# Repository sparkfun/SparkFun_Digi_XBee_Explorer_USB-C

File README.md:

SparkFun Digi XBee® Explorer USB-C
========================================

[*SparkFun Digi XBee® Explorer USB-C (22043)*](https://www.sparkfun.com/products/22043)

<Basic description of the part.>

Repository Contents
-------------------

* **/Hardware** - Eagle design files (.brd, .sch)
* **/Production** - Production panel files (.brd)

Documentation
--------------
* **[Hookup Guide](http://docs.sparkfun.com/SparkFun_Digi_XBee_Explorer_USB-C)** - Basic hookup guide for the SparkFun Digi XBee® Explorer USB-C.

License Information
-------------------

This product is _**open source**_! 

Please review the LICENSE.md file for license information. 

If you have any questions or concerns on licensing, please contact technical support on our [SparkFun forums](https://forum.sparkfun.com/viewforum.php?f=152).

Distributed as-is; no warranty is given.

- Your friends at SparkFun.

_<COLLABORATION CREDIT>_

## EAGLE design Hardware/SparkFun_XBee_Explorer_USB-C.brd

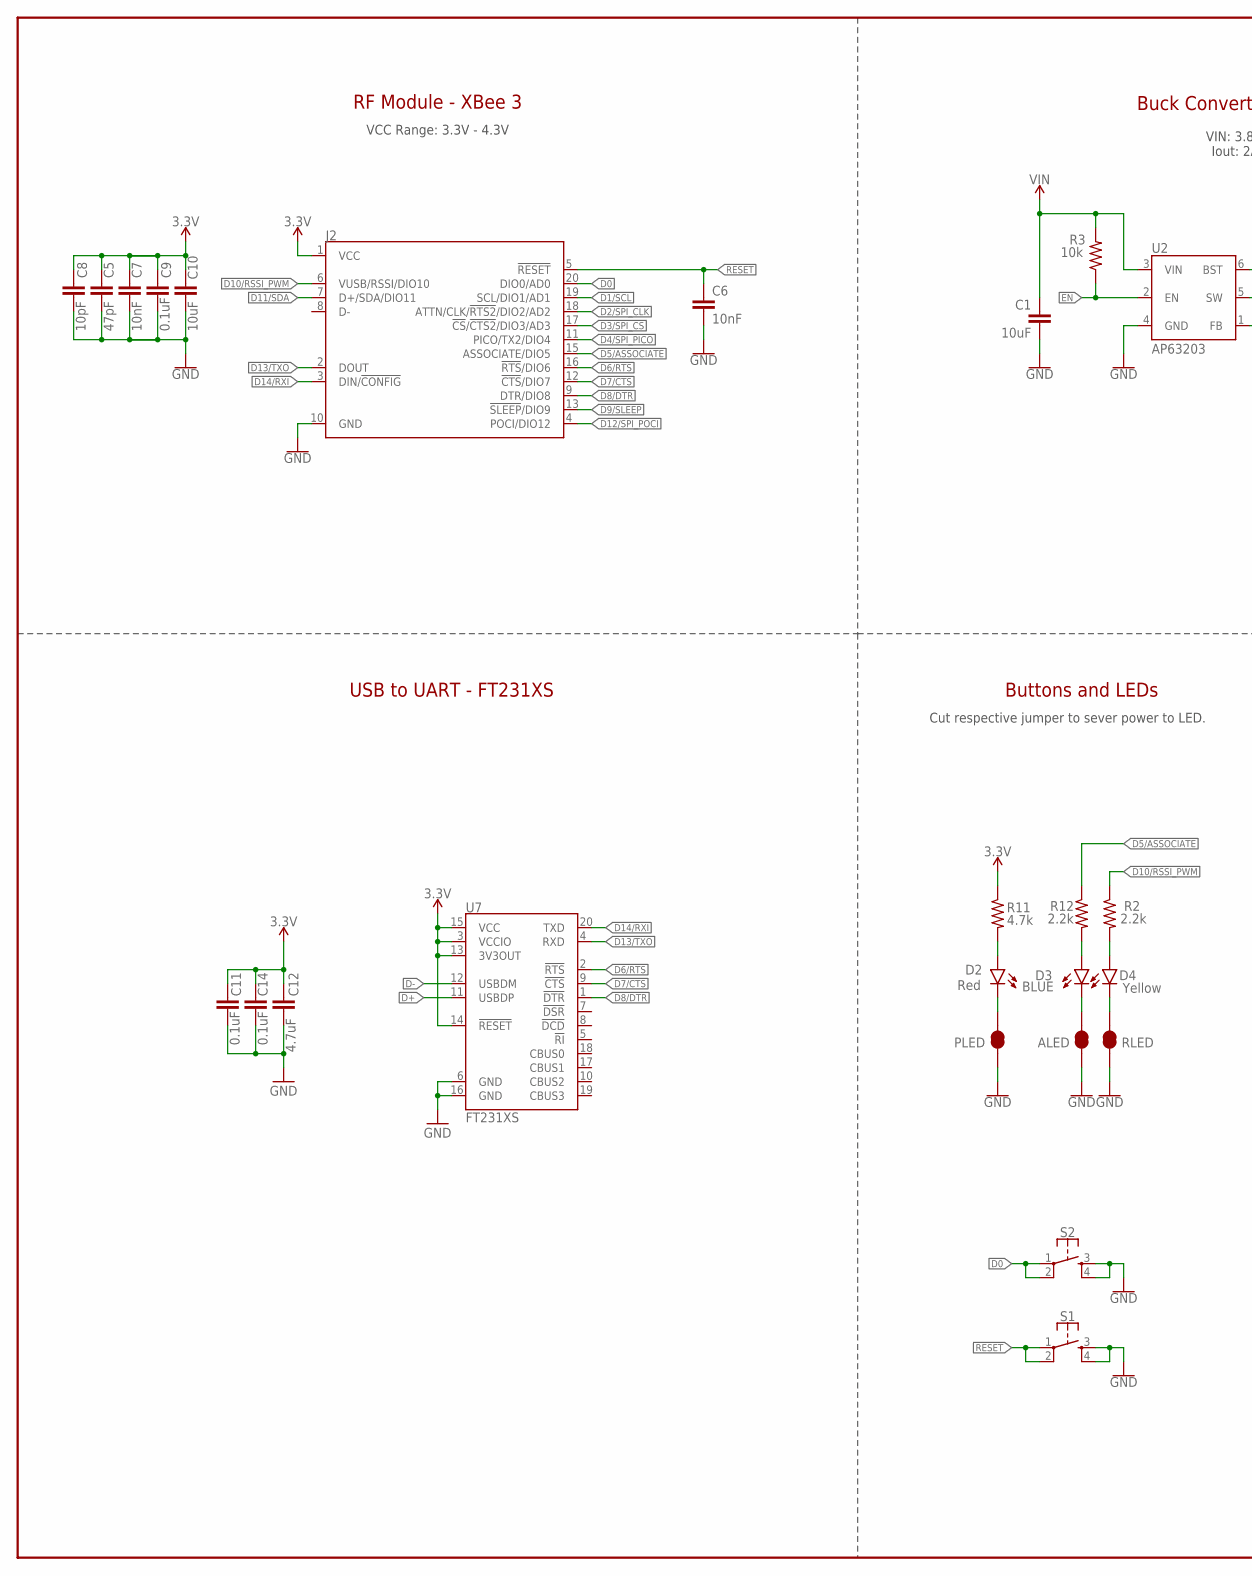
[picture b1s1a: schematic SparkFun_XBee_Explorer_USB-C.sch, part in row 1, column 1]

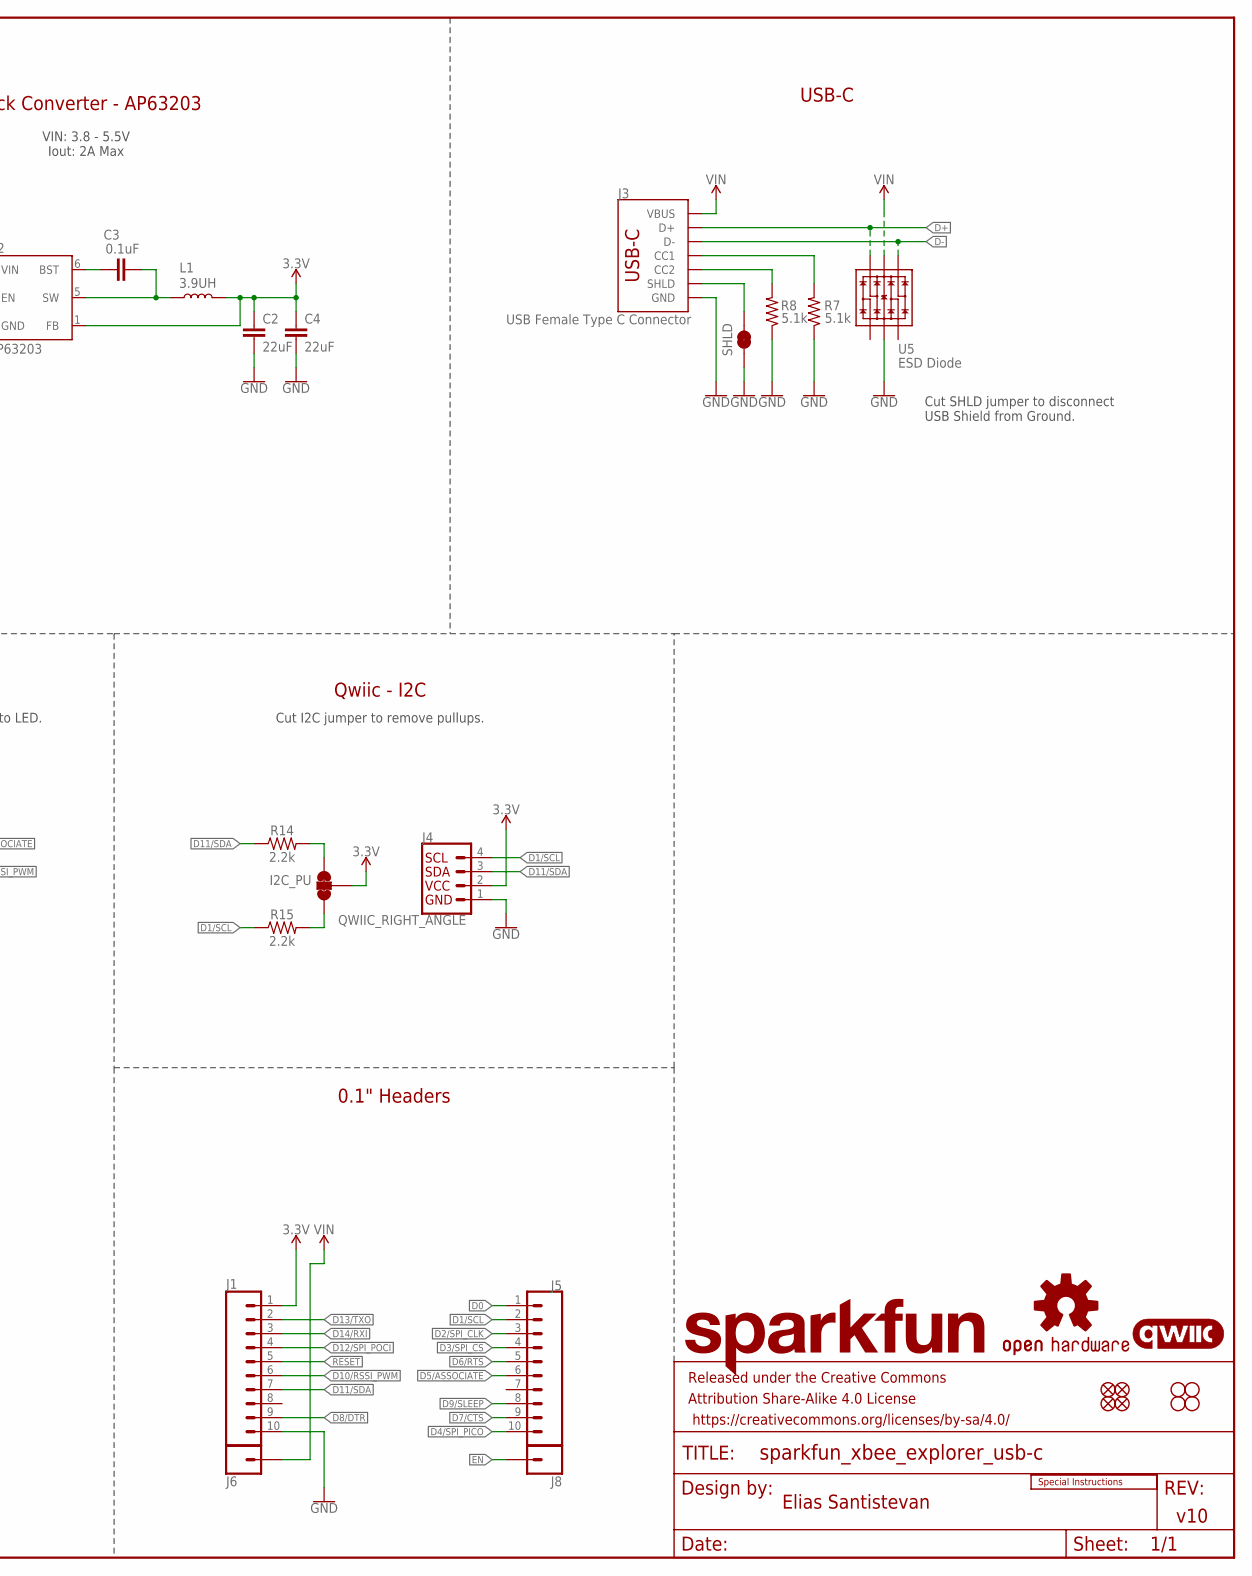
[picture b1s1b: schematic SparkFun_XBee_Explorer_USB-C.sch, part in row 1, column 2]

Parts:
ALED: JUMPER-SMT_2_NC_TRACE_SILK; SMT-JUMPER_2_NC_TRACE_SILK
C1: 10uF; 1210
C2, C4: 22uF; 0603
C3, C9, C11, C14: 0.1uF; 0603
C5: 47pF; 0603
C6, C7: 10nF; 0603
C8: 10pF; 0603
C10: 10uF; 0603
C12: 4.7uF; 0603
D2: Red; LED-0603
D3: BLUE; LED-0603
D4: Yellow; LED-0603
FD1, FD2, FD3, FD4: FIDUCIAL1X2; FIDUCIAL-1X2
FRAME1: FRAME-LEDGER; CREATIVE_COMMONS
H1, H2, H3, H4: STAND-OFFTIGHT; STAND-OFF-TIGHT
I2C_PU: JUMPER-SMT_3_2-NC_TRACE_SILK; SMT-JUMPER_3_2-NC_TRACE_SILK
J1, J8: CONN_01PTH_NO_SILK_STAND; 1X01_NO_SILK_STAND
J2: XBEE_UPDATEXBEE_SMD; XBEE3-SMD
J3: USB Female Type C Connector; USB-C-16P-4LAYER-ISOLATED
J4: QWIIC_RIGHT_ANGLE; JST04_1MM_RA
J5, J6: CONN_10NO_SILK_PTH_FEMALE; 1X10_NO_SILK
L1: 3.9UH; INDUCTOR_3.9UH
LOGO1: SFE_LOGO_NAME.2_INCH; SFE_LOGO_NAME_.2
LOGO2: OSHW-LOGOS; OSHW-LOGO-S
LOGO3: QWIIC_LOGO_4MM; QWIIC_4MM
LOGO4: SPECIAL_INSTRUCTIONS-ORDERING; ORDERING_INSTRUCTIONS
PLED: JUMPER-SMT_2_NC_TRACE_SILK; SMT-JUMPER_2_NC_TRACE_SILK
R2, R12, R14, R15: 2.2k; 0603
R3: 10k; 0603
R7, R8: 5.1k; 0603
R11: 4.7k; 0603
RLED: JUMPER-SMT_2_NC_TRACE_SILK; SMT-JUMPER_2_NC_TRACE_SILK
S1, S2: MOMENTARY-SWITCH-SPST-2-SMD-5.2MM-TALL; TACTILE_SWITCH_SMD_5.2MM
SHLD: JUMPER-SMT_2_NC_TRACE_SILK; SMT-JUMPER_2_NC_TRACE_SILK
U2: AP63203; SOT23-6
U5: ESD Diode; SOT-23-6
U7: FT231XS; SSOP20_L

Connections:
3.3V: C2.1, C4.1, C5.1, C7.1, C8.1, C9.1, C10.1, C11.1, C12.1, C14.1, I2C_PU.2, J2.1 (VCC), J4.2, J6.1, L1.P$2 (2), R11.1, U2.1 (FB), U7.3 (VCCIO), U7.13 (3V3OUT), U7.14 (!RESET), U7.15 (VCC)
!RESET!: C6.1, J2.5 (!RESET!), J6.5, S1.1, S1.2
D0: J2.20 (DIO0/AD0), J5.1, S2.1, S2.2
D1/SCL: J2.19 (SCL/DIO1/AD1), J4.4, J5.2, R15.1
D2/SPI_CLK: J2.18 (ATTN/CLK/!RTS2!/DIO2/AD2), J5.3
D3/SPI_!CS!: J2.17 (!CS!/!CTS2!/DIO3/AD3), J5.4
D4/SPI_PICO: J2.11 (PICO/TX2/DIO4), J5.10
D5/ASSOCIATE: J2.15 (ASSOCIATE/DIO5), J5.6, R12.1
D6/!RTS!: J2.16 (!RTS!/DIO6), J5.5, U7.2 (!RTS)
D7/!CTS!: J2.12 (!CTS!/DIO7), J5.9, U7.9 (!CTS)
D8/!DTR!: J2.9 (DTR/DIO8), J6.9, U7.1 (!DTR)
D9/!SLEEP!: J2.13 (!SLEEP!/DIO9), J5.8
D10/RSSI_PWM: J2.6 (VUSB/RSSI/DIO10), J6.6, R2.1
D11/SDA: J2.7 (D+/SDA/DIO11), J4.3, J6.7, R14.1
D12/SPI_POCI: J2.4 (POCI/DIO12), J6.4
D13/TXO: J2.2 (DOUT), J6.2, U7.4 (RXD)
D14/RXI: J2.3 (DIN/!CONFIG!), J6.3, U7.20 (TXD)
D+: J3.A6 (D+), J3.B6 (D+), U5.6 (IO4), U7.11 (USBDP)
D-: J3.A7 (D-), J3.B7 (D-), U5.4 (IO3), U7.12 (USBDM)
EN: J8.1, R3.1, U2.2 (EN)
GND: ALED.1, C1.2, C2.2, C4.2, C5.2, C6.2, C7.2, C8.2, C9.2, C10.2, C11.2, C12.2, C14.2, J2.10 (GND), J3.GND, J3.GND2 (GND), J4.1, J6.10, PLED.1, R7.1, R8.1, RLED.1, S1.3, S1.4, S2.3, S2.4, SHLD.1, U2.4 (GND), U5.2 (VSS), U7.6 (GND), U7.16 (GND)
unnamed: C3.1, U2.6 (BST)
unnamed: D4.A, R2.2
unnamed: D4.C, RLED.2
unnamed: J3.B5 (CC2), R8.2
unnamed: J3.A5 (CC1), R7.2
unnamed: D2.A, R11.2
unnamed: C3.2, L1.P$1 (1), U2.5 (SW)
unnamed: I2C_PU.3, R14.2
unnamed: D3.A, R12.2
unnamed: I2C_PU.1, R15.2
unnamed: ALED.2, D3.C
unnamed: D2.C, PLED.2
SHLD: J3.SHLD1 (SHLD), J3.SHLD2 (SHLD), J3.SHLD3 (SHLD), J3.SHLD4 (SHLD), J3.SHLD5 (SHLD), J3.SHLD6 (SHLD), J3.SHLD7 (SHLD), J3.SHLD8 (SHLD), SHLD.2
VIN: C1.1, J1.1, J3.VBUS1 (VBUS), J3.VBUS2 (VBUS), R3.2, U2.3 (VIN), U5.5 (VCC)

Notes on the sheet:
VCC Range: 3.3V - 4.3V
Buck Converter - AP63203
Qwiic - I2C
v10
Elias Santistevan
Buttons and LEDs
VIN: 3.8 - 5.5V Iout: 2A Max
Cut I2C jumper to remove pullups.
Cut respective jumper to sever power to LED.
RF Module - XBee 3
0.1" Headers
Cut SHLD jumper to disconnect USB Shield from Ground.
USB to UART - FT231XS
USB-C

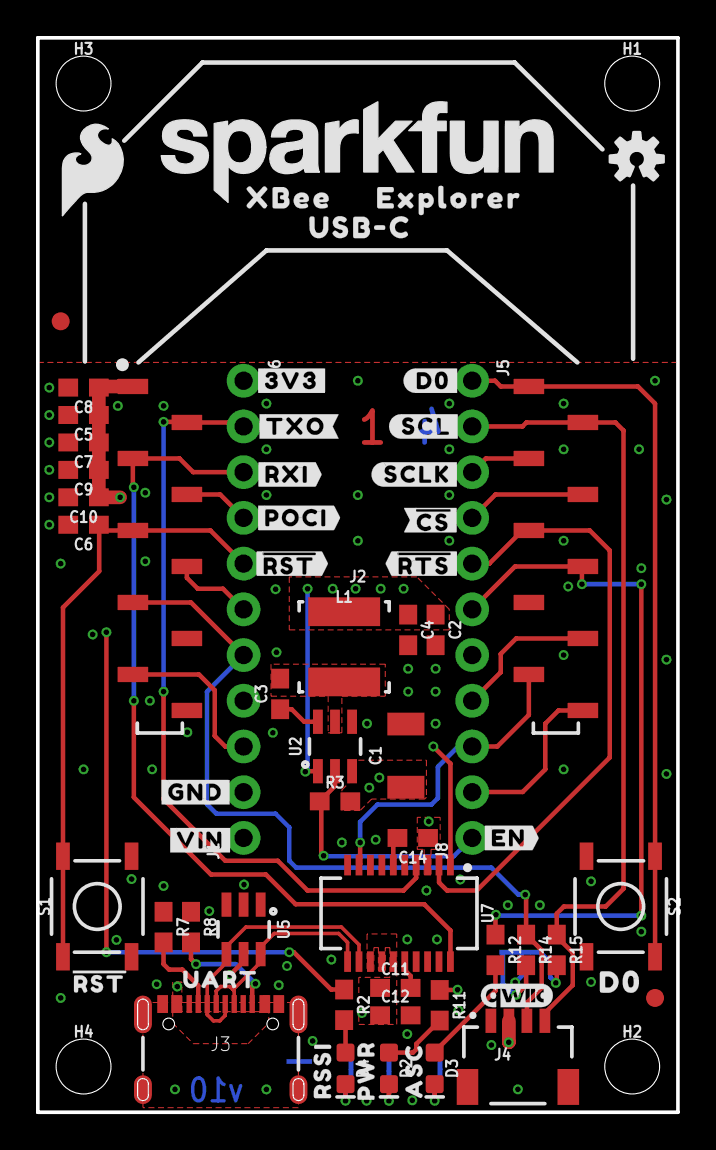
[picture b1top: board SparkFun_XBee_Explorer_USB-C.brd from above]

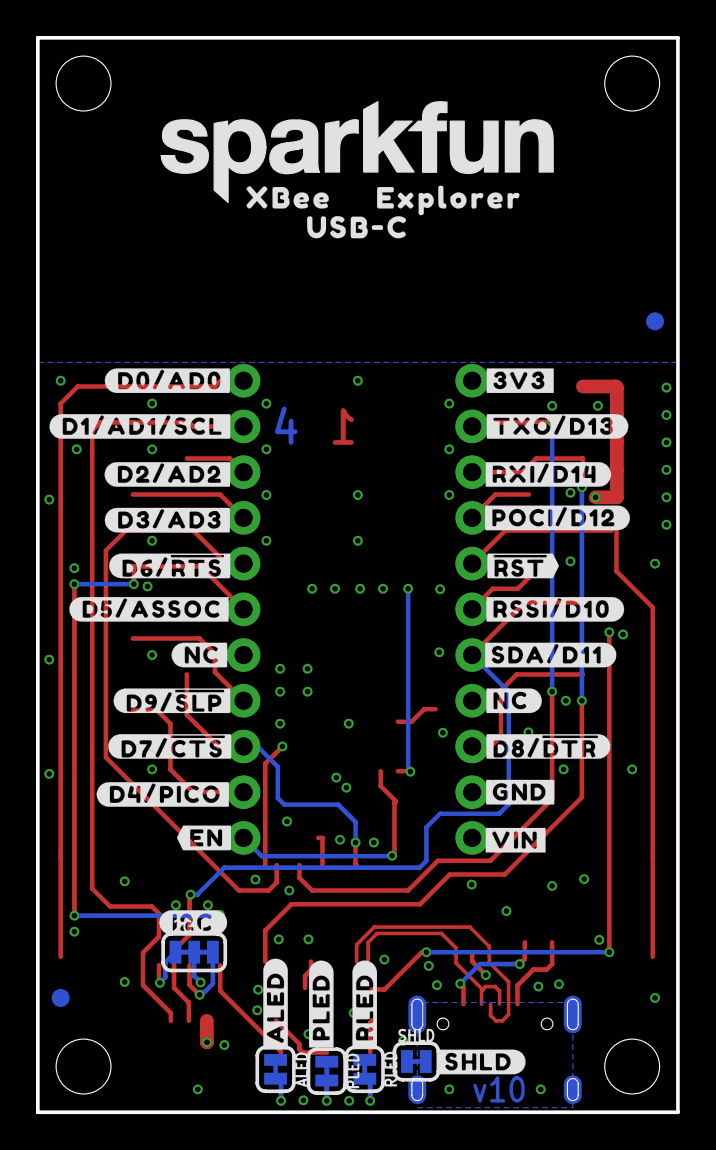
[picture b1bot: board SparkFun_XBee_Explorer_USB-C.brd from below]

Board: 4 copper layers, 35.6 x 59.7 mm, 109 parts (38 on the bottom side), 35 nets.

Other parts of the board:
U$1: RSSI31
U$2: PWR29
U$3, U$12: #GND#0
U$4: #SHLD#36
U$5: #NC#1
U$6: #D3#AD3#23
U$7: #NC#3
U$8: #D0#AD0#18
U$9, U$44: #3V3#1
U$10, U$23: XBEE340
U$11: #D1#AD1#SCL#8
U$13: #D8##DTR##27
U$14: #RSSI#D10#17
U$15: #SDA#D11#9
U$16: ##RST##15
U$17: #POCI#D12#24
U$18: #RXI#D14#15
U$19: #D2#AD2#19
U$20: #D6##RTS##25
U$21: #TXO#8
U$22: #TXO#D13#13
U$24, U$25: USB#C1342
U$26: #I2C#33
U$27: #RXI#7
U$28: UART34
U$29: ASC32
U$30: #RST#30
U$31, U$32: EXPLORER1344
U$35: #D5#ASSOC#25
U$36: #D9##SLP##28
U$37: #D7##CTS##26
U$38: #D4#PICO#25
U$40: D03
U$45: #POCI#32
U$46, U$66: #VIN#4
U$48: #EN#17
U$49: #ALED#21
U$51: #RLED#22
U$52: #PLED#20
U$54: ##RST##13
U$58: ##RTS##14
U$59: ##CS##26
U$60: #SCLK#33
U$61: SFE_LOGO_FLAME_.2
U$63: SFE_LOGO_NAME_.2
U$64: #SCL#9
U$65: #D0#3
U$67: #EN#15

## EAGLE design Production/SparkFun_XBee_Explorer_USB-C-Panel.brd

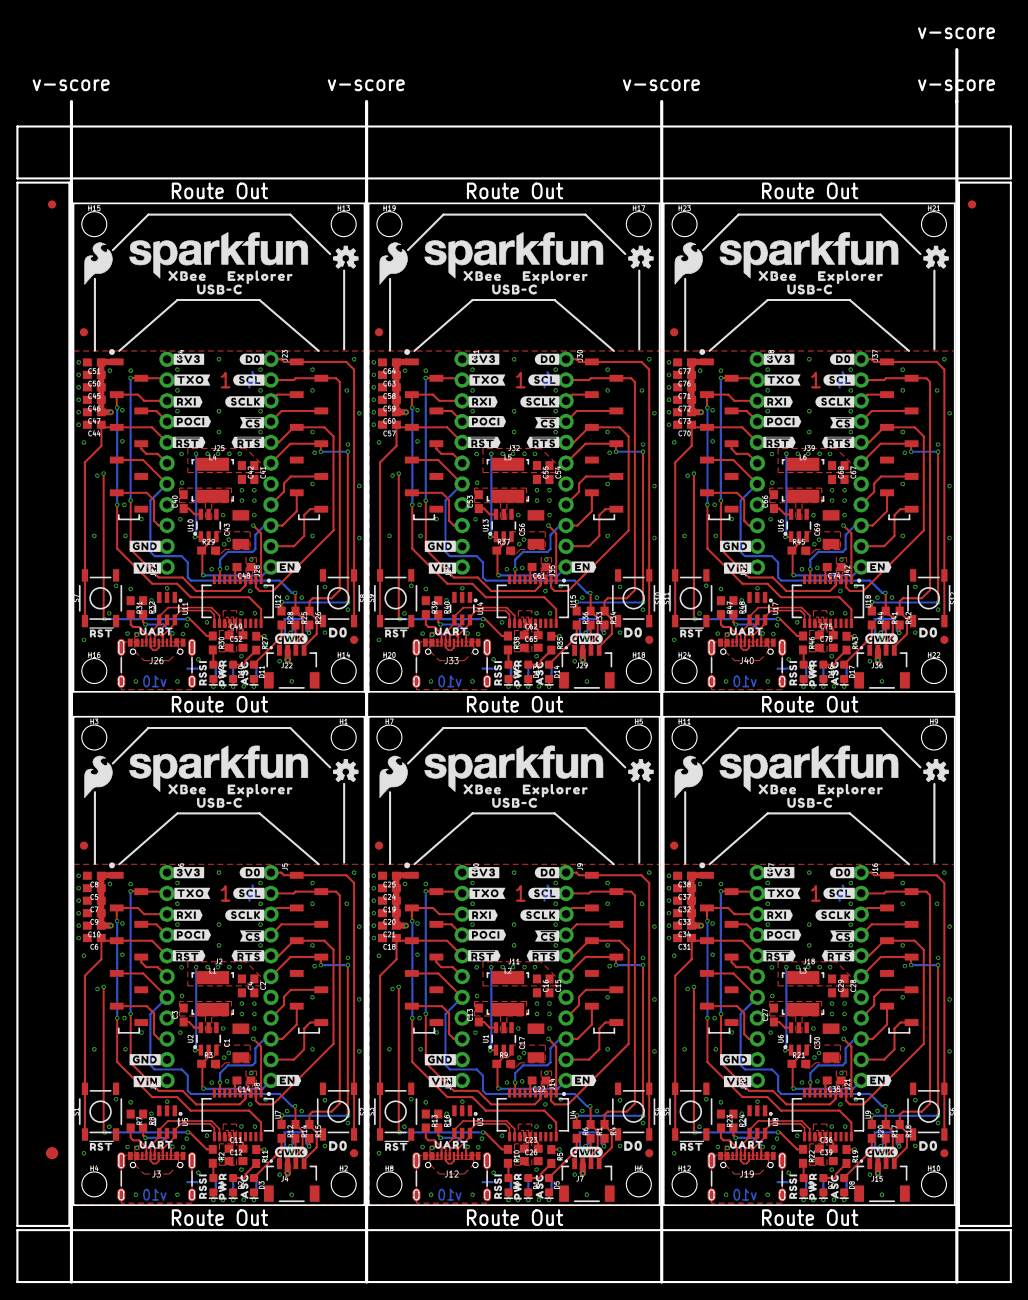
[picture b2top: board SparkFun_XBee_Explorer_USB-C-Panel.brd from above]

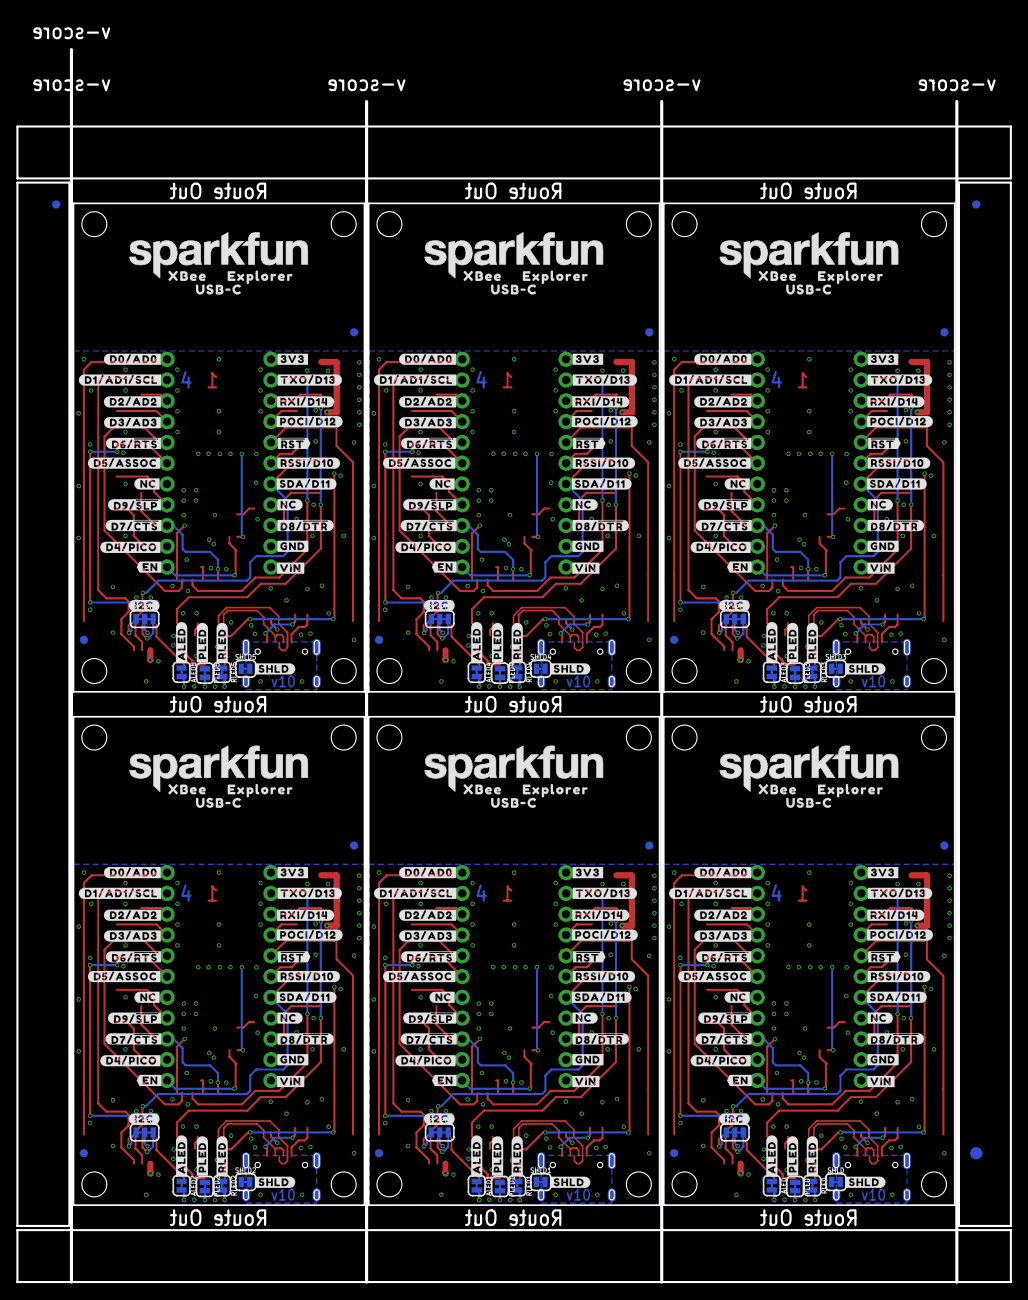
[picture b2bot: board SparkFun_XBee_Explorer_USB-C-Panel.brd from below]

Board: 4 copper layers, 121.4 x 150.6 mm, 648 parts (231 on the bottom side), 210 nets.

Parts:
ALED, ALED1, ALED2, ALED3, ALED4, ALED5: JUMPER-SMT_2_NC_TRACE_SILK; SMT-JUMPER_2_NC_TRACE_SILK
C1, C17, C30, C43, C56, C69: 10uF; 1210
C2, C4, C15, C16, C28, C29, C41, C42, C54, C55, C67, C68: 22uF; 0603
C3, C9, C11, C13, C14, C20, C22, C23, C27, C33, C35, C36, C40, C46, C48, C49, C53, C59, C61, C62, C66, C72, C74, C75: 0.1uF; 0603
C5, C24, C37, C50, C63, C76: 47pF; 0603
C6, C7, C18, C19, C31, C32, C44, C45, C57, C58, C70, C71: 10nF; 0603
C8, C25, C38, C51, C64, C77: 10pF; 0603
C10, C21, C34, C47, C60, C73: 10uF; 0603
C12, C26, C39, C52, C65, C78: 4.7uF; 0603
D1, D2, D7, D10, D13, D16: Red; LED-0603
D3, D5, D8, D11, D14, D17: BLUE; LED-0603
D4, D6, D9, D12, D15, D18: Yellow; LED-0603
E$1, E$2, E$3, E$4: FIDUCIAL-1X2
E$5, E$6: FIDUCIAL-1.5X3
FD1, FD2, FD3, FD4, FD5, FD6, FD7, FD8, FD9, FD10, FD11, FD12, FD13, FD14, FD15, FD16, FD17, FD18, FD19, FD20, FD21, FD22, FD23, FD24: FIDUCIAL1X2; FIDUCIAL-1X2
H1, H2, H3, H4, H5, H6, H7, H8, H9, H10, H11, H12, H13, H14, H15, H16, H17, H18, H19, H20, H21, H22, H23, H24: STAND-OFFTIGHT; STAND-OFF-TIGHT
I2C_PU, I2C_PU1, I2C_PU2, I2C_PU3, I2C_PU4, I2C_PU5: JUMPER-SMT_3_2-NC_TRACE_SILK; SMT-JUMPER_3_2-NC_TRACE_SILK
J1, J8, J13, J14, J20, J21, J27, J28, J34, J35, J41, J42: 1X01_NO_SILK_STAND
J2, J11, J18, J25, J32, J39: XBEE3-SMD
J3, J12, J19, J26, J33, J40: USB Female Type C Connector; USB-C-16P-4LAYER-ISOLATED
J4, J7, J15, J22, J29, J36: QWIIC_RIGHT_ANGLE; JST04_1MM_RA
J5, J6, J9, J10, J16, J17, J23, J24, J30, J31, J37, J38: 1X10_NO_SILK
L1, L2, L3, L4, L5, L6: 3.9UH; INDUCTOR_3.9UH
LOGO1, LOGO6, LOGO9, LOGO12, LOGO15, LOGO18: SFE_LOGO_NAME.2_INCH; SFE_LOGO_NAME_.2
LOGO2, LOGO4, LOGO7, LOGO10, LOGO13, LOGO16: OSHW-LOGOS; OSHW-LOGO-S
LOGO3, LOGO5, LOGO8, LOGO11, LOGO14, LOGO17: QWIIC_LOGO_4MM; QWIIC_4MM
PLED, PLED1, PLED2, PLED3, PLED4, PLED5: JUMPER-SMT_2_NC_TRACE_SILK; SMT-JUMPER_2_NC_TRACE_SILK
R1, R2, R4, R6, R10, R12, R14, R15, R17, R18, R20, R22, R25, R26, R28, R30, R33, R34, R36, R38, R41, R42, R44, R46: 2.2k; 0603
R3, R9, R21, R29, R37, R45: 10k; 0603
R5, R11, R19, R27, R35, R43: 4.7k; 0603
R7, R8, R13, R16, R23, R24, R31, R32, R39, R40, R47, R48: 5.1k; 0603
RLED, RLED1, RLED2, RLED3, RLED4, RLED5: JUMPER-SMT_2_NC_TRACE_SILK; SMT-JUMPER_2_NC_TRACE_SILK
S1, S2, S3, S4, S5, S6, S7, S8, S9, S10, S11, S12: TACTILE_SWITCH_SMD_5.2MM
SHLD, SHLD1, SHLD2, SHLD3, SHLD4, SHLD5: JUMPER-SMT_2_NC_TRACE_SILK; SMT-JUMPER_2_NC_TRACE_SILK
U1, U2, U6, U10, U13, U16: AP63203; SOT23-6
U3, U5, U8, U11, U14, U17: ESD Diode; SOT-23-6
U4, U7, U9, U12, U15, U18: FT231XS; SSOP20_L
U$1, U$104, U$158, U$212, U$266, U$320: RSSI31
U$2, U$105, U$159, U$213, U$267, U$321: PWR29
U$3, U$12, U$71, U$100, U$125, U$154, U$179, U$208, U$233, U$262, U$287, U$316: #GND#0
U$4, U$94, U$148, U$202, U$256, U$310: #SHLD#36
U$5, U$95, U$149, U$203, U$257, U$311: #NC#1
U$6, U$56, U$119, U$173, U$227, U$281: #D3#AD3#23
U$7, U$96, U$150, U$204, U$258, U$312: #NC#3
U$8, U$53, U$117, U$171, U$225, U$279: #D0#AD0#18
U$9, U$33, U$39, U$44, U$109, U$111, U$163, U$165, U$217, U$219, U$271, U$273: #3V3#1
U$10, U$23, U$101, U$102, U$155, U$156, U$209, U$210, U$263, U$264, U$317, U$318: XBEE340
U$11, U$106, U$160, U$214, U$268, U$322: #D1#AD1#SCL#8
U$13, U$72, U$126, U$180, U$234, U$288: #D8##DTR##27
U$14, U$73, U$127, U$181, U$235, U$289: #RSSI#D10#17
U$15, U$74, U$128, U$182, U$236, U$290: #SDA#D11#9
U$16, U$75, U$129, U$183, U$237, U$291: ##RST##15
U$17, U$76, U$130, U$184, U$238, U$292: #POCI#D12#24
U$18, U$77, U$131, U$185, U$239, U$293: #RXI#D14#15
U$19, U$55, U$118, U$172, U$226, U$280: #D2#AD2#19
U$20, U$57, U$120, U$174, U$228, U$282: #D6##RTS##25
U$21, U$83, U$137, U$191, U$245, U$299: #TXO#8
U$22, U$78, U$132, U$186, U$240, U$294: #TXO#D13#13
U$24, U$25, U$97, U$98, U$151, U$152, U$205, U$206, U$259, U$260, U$313, U$314: USB#C1342
U$26, U$34, U$110, U$164, U$218, U$272: #I2C#33
U$27, U$84, U$138, U$192, U$246, U$300: #RXI#7
U$28, U$99, U$153, U$207, U$261, U$315: UART34
U$29, U$103, U$157, U$211, U$265, U$319: ASC32
U$30, U$43, U$114, U$168, U$222, U$276: #RST#30
U$31, U$32, U$107, U$108, U$161, U$162, U$215, U$216, U$269, U$270, U$323, U$324: EXPLORER1344
U$35, U$62, U$121, U$175, U$229, U$283: #D5#ASSOC#25
U$36, U$68, U$122, U$176, U$230, U$284: #D9##SLP##28
U$37, U$69, U$123, U$177, U$231, U$285: #D7##CTS##26
U$38, U$70, U$124, U$178, U$232, U$286: #D4#PICO#25
U$40, U$42, U$113, U$167, U$221, U$275: D03
U$41, U$46, U$66, U$92, U$112, U$146, U$166, U$200, U$220, U$254, U$274, U$308: #VIN#4
U$45, U$85, U$139, U$193, U$247, U$301: #POCI#32
U$47, U$63, U$115, U$169, U$223, U$277: SFE_LOGO_NAME_.2
U$48, U$79, U$133, U$187, U$241, U$295: #EN#17
U$49, U$80, U$134, U$188, U$242, U$296: #ALED#21
U$50, U$61, U$116, U$170, U$224, U$278: SFE_LOGO_FLAME_.2
U$51, U$81, U$135, U$189, U$243, U$297: #RLED#22
U$52, U$82, U$136, U$190, U$244, U$298: #PLED#20
U$54, U$86, U$140, U$194, U$248, U$302: ##RST##13
U$58, U$87, U$141, U$195, U$249, U$303: ##RTS##14
U$59, U$88, U$142, U$196, U$250, U$304: ##CS##26
U$60, U$89, U$143, U$197, U$251, U$305: #SCLK#33
U$64, U$90, U$144, U$198, U$252, U$306: #SCL#9
U$65, U$91, U$145, U$199, U$253, U$307: #D0#3
U$67, U$93, U$147, U$201, U$255, U$309: #EN#15

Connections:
3.3V: C2.1, C4.1, C5.1, C7.1, C8.1, C9.1, C10.1, C11.1, C12.1, C14.1, I2C_PU.2, J2.1, J4.2, J6.1, L1.P$2, R11.1, U2.1, U7.3, U7.13, U7.14, U7.15
3.3V1: C15.1, C16.1, C19.1, C20.1, C21.1, C22.1, C23.1, C24.1, C25.1, C26.1, I2C_PU1.2, J7.2, J10.1, J11.1, L2.P$2, R5.1, U1.1, U4.3, U4.13, U4.14, U4.15
3.3V2: C28.1, C29.1, C32.1, C33.1, C34.1, C35.1, C36.1, C37.1, C38.1, C39.1, I2C_PU2.2, J15.2, J17.1, J18.1, L3.P$2, R19.1, U6.1, U9.3, U9.13, U9.14, U9.15
3.3V3: C41.1, C42.1, C45.1, C46.1, C47.1, C48.1, C49.1, C50.1, C51.1, C52.1, I2C_PU3.2, J22.2, J24.1, J25.1, L4.P$2, R27.1, U10.1, U12.3, U12.13, U12.14, U12.15
3.3V4: C54.1, C55.1, C58.1, C59.1, C60.1, C61.1, C62.1, C63.1, C64.1, C65.1, I2C_PU4.2, J29.2, J31.1, J32.1, L5.P$2, R35.1, U13.1, U15.3, U15.13, U15.14, U15.15
3.3V5: C67.1, C68.1, C71.1, C72.1, C73.1, C74.1, C75.1, C76.1, C77.1, C78.1, I2C_PU5.2, J36.2, J38.1, J39.1, L6.P$2, R43.1, U16.1, U18.3, U18.13, U18.14, U18.15
!RESET!: C6.1, J2.5, J6.5, S1.1, S1.2
!RESET!1: C18.1, J10.5, J11.5, S3.1, S3.2
!RESET!2: C31.1, J17.5, J18.5, S5.1, S5.2
!RESET!3: C44.1, J24.5, J25.5, S7.1, S7.2
!RESET!4: C57.1, J31.5, J32.5, S9.1, S9.2
!RESET!5: C70.1, J38.5, J39.5, S11.1, S11.2
D0: J2.20, J5.1, S2.1, S2.2
D1: J9.1, J11.20, S4.1, S4.2
D1/SCL: J2.19, J4.4, J5.2, R15.1
D1/SCL1: J7.4, J9.2, J11.19, R4.1
D1/SCL2: J15.4, J16.2, J18.19, R18.1
D1/SCL3: J22.4, J23.2, J25.19, R26.1
D1/SCL4: J29.4, J30.2, J32.19, R34.1
D1/SCL5: J36.4, J37.2, J39.19, R42.1
D2: J16.1, J18.20, S6.1, S6.2
D2/SPI_CLK: J2.18, J5.3
D2/SPI_CLK1: J9.3, J11.18
D2/SPI_CLK2: J16.3, J18.18
D2/SPI_CLK3: J23.3, J25.18
D2/SPI_CLK4: J30.3, J32.18
D2/SPI_CLK5: J37.3, J39.18
D3: J23.1, J25.20, S8.1, S8.2
D3/SPI_!CS!: J2.17, J5.4
D3/SPI_!CS!1: J9.4, J11.17
D3/SPI_!CS!2: J16.4, J18.17
D3/SPI_!CS!3: J23.4, J25.17
D3/SPI_!CS!4: J30.4, J32.17
D3/SPI_!CS!5: J37.4, J39.17
D4: J30.1, J32.20, S10.1, S10.2
D4/SPI_PICO: J2.11, J5.10
D4/SPI_PICO1: J9.10, J11.11
D4/SPI_PICO2: J16.10, J18.11
D4/SPI_PICO3: J23.10, J25.11
D4/SPI_PICO4: J30.10, J32.11
D4/SPI_PICO5: J37.10, J39.11
D5: J37.1, J39.20, S12.1, S12.2
D5/ASSOCIATE: J2.15, J5.6, R12.1
D5/ASSOCIATE1: J9.6, J11.15, R6.1
D5/ASSOCIATE2: J16.6, J18.15, R20.1
D5/ASSOCIATE3: J23.6, J25.15, R28.1
D5/ASSOCIATE4: J30.6, J32.15, R36.1
D5/ASSOCIATE5: J37.6, J39.15, R44.1
D6/!RTS!: J2.16, J5.5, U7.2
D6/!RTS!1: J9.5, J11.16, U4.2
D6/!RTS!2: J16.5, J18.16, U9.2
D6/!RTS!3: J23.5, J25.16, U12.2
D6/!RTS!4: J30.5, J32.16, U15.2
D6/!RTS!5: J37.5, J39.16, U18.2
D7/!CTS!: J2.12, J5.9, U7.9
D7/!CTS!1: J9.9, J11.12, U4.9
D7/!CTS!2: J16.9, J18.12, U9.9
D7/!CTS!3: J23.9, J25.12, U12.9
D7/!CTS!4: J30.9, J32.12, U15.9
D7/!CTS!5: J37.9, J39.12, U18.9
D8/!DTR!: J2.9, J6.9, U7.1
D8/!DTR!1: J10.9, J11.9, U4.1
D8/!DTR!2: J17.9, J18.9, U9.1
D8/!DTR!3: J24.9, J25.9, U12.1
D8/!DTR!4: J31.9, J32.9, U15.1
D8/!DTR!5: J38.9, J39.9, U18.1
D9/!SLEEP!: J2.13, J5.8
D9/!SLEEP!1: J9.8, J11.13
D9/!SLEEP!2: J16.8, J18.13
D9/!SLEEP!3: J23.8, J25.13
D9/!SLEEP!4: J30.8, J32.13
D9/!SLEEP!5: J37.8, J39.13
D10/RSSI_PWM: J2.6, J6.6, R2.1
D10/RSSI_PWM1: J10.6, J11.6, R10.1
D10/RSSI_PWM2: J17.6, J18.6, R22.1
D10/RSSI_PWM3: J24.6, J25.6, R30.1
D10/RSSI_PWM4: J31.6, J32.6, R38.1
D10/RSSI_PWM5: J38.6, J39.6, R46.1
D11/SDA: J2.7, J4.3, J6.7, R14.1
D11/SDA1: J7.3, J10.7, J11.7, R1.1
D11/SDA2: J15.3, J17.7, J18.7, R17.1
D11/SDA3: J22.3, J24.7, J25.7, R25.1
D11/SDA4: J29.3, J31.7, J32.7, R33.1
D11/SDA5: J36.3, J38.7, J39.7, R41.1
D12/SPI_POCI: J2.4, J6.4
D12/SPI_POCI1: J10.4, J11.4
D12/SPI_POCI2: J17.4, J18.4
D12/SPI_POCI3: J24.4, J25.4
D12/SPI_POCI4: J31.4, J32.4
D12/SPI_POCI5: J38.4, J39.4
D13/TXO: J2.2, J6.2, U7.4
D13/TXO1: J10.2, J11.2, U4.4
D13/TXO2: J17.2, J18.2, U9.4
D13/TXO3: J24.2, J25.2, U12.4
D13/TXO4: J31.2, J32.2, U15.4
D13/TXO5: J38.2, J39.2, U18.4
D14/RXI: J2.3, J6.3, U7.20
D14/RXI1: J10.3, J11.3, U4.20
D14/RXI2: J17.3, J18.3, U9.20
D14/RXI3: J24.3, J25.3, U12.20
D14/RXI4: J31.3, J32.3, U15.20
D14/RXI5: J38.3, J39.3, U18.20
D+: J3.A6, J3.B6, U5.6, U7.11
D+1: J12.A6, J12.B6, U3.6, U4.11
D+2: J19.A6, J19.B6, U8.6, U9.11
D+3: J26.A6, J26.B6, U11.6, U12.11
D+4: J33.A6, J33.B6, U14.6, U15.11
D+5: J40.A6, J40.B6, U17.6, U18.11
D-: J3.A7, J3.B7, U5.4, U7.12
D-1: J12.A7, J12.B7, U3.4, U4.12
D-2: J19.A7, J19.B7, U8.4, U9.12
D-3: J26.A7, J26.B7, U11.4, U12.12
D-4: J33.A7, J33.B7, U14.4, U15.12
D-5: J40.A7, J40.B7, U17.4, U18.12
EN: J8.1, R3.1, U2.2
EN1: J14.1, R9.1, U1.2
EN2: J21.1, R21.1, U6.2
EN3: J28.1, R29.1, U10.2
EN4: J35.1, R37.1, U13.2
EN5: J42.1, R45.1, U16.2
GND: ALED.1, C1.2, C2.2, C4.2, C5.2, C6.2, C7.2, C8.2, C9.2, C10.2, C11.2, C12.2, C14.2, J2.10, J3.GND, J3.GND2, J4.1, J6.10, PLED.1, R7.1, R8.1, RLED.1, S1.3, S1.4, S2.3, S2.4, SHLD.1, U2.4, U5.2, U7.6, U7.16
GND1: ALED1.1, C15.2, C16.2, C17.2, C18.2, C19.2, C20.2, C21.2, C22.2, C23.2, C24.2, C25.2, C26.2, J7.1, J10.10, J11.10, J12.GND, J12.GND2, PLED1.1, R13.1, R16.1, RLED1.1, S3.3, S3.4, S4.3, S4.4, SHLD1.1, U1.4, U3.2, U4.6, U4.16
GND2: ALED2.1, C28.2, C29.2, C30.2, C31.2, C32.2, C33.2, C34.2, C35.2, C36.2, C37.2, C38.2, C39.2, J15.1, J17.10, J18.10, J19.GND, J19.GND2, PLED2.1, R23.1, R24.1, RLED2.1, S5.3, S5.4, S6.3, S6.4, SHLD2.1, U6.4, U8.2, U9.6, U9.16
GND3: ALED3.1, C41.2, C42.2, C43.2, C44.2, C45.2, C46.2, C47.2, C48.2, C49.2, C50.2, C51.2, C52.2, J22.1, J24.10, J25.10, J26.GND, J26.GND2, PLED3.1, R31.1, R32.1, RLED3.1, S7.3, S7.4, S8.3, S8.4, SHLD3.1, U10.4, U11.2, U12.6, U12.16
GND4: ALED4.1, C54.2, C55.2, C56.2, C57.2, C58.2, C59.2, C60.2, C61.2, C62.2, C63.2, C64.2, C65.2, J29.1, J31.10, J32.10, J33.GND, J33.GND2, PLED4.1, R39.1, R40.1, RLED4.1, S9.3, S9.4, S10.3, S10.4, SHLD4.1, U13.4, U14.2, U15.6, U15.16
GND5: ALED5.1, C67.2, C68.2, C69.2, C70.2, C71.2, C72.2, C73.2, C74.2, C75.2, C76.2, C77.2, C78.2, J36.1, J38.10, J39.10, J40.GND, J40.GND2, PLED5.1, R47.1, R48.1, RLED5.1, S11.3, S11.4, S12.3, S12.4, SHLD5.1, U16.4, U17.2, U18.6, U18.16
unnamed: C3.1, U2.6
unnamed: D4.A, R2.2
unnamed: D4.C, RLED.2
unnamed: I2C_PU1.3, R1.2
unnamed: J3.B5, R8.2
unnamed: J3.A5, R7.2
unnamed: D2.A, R11.2
unnamed: C3.2, L1.P$1, U2.5
unnamed: I2C_PU1.1, R4.2
unnamed: D1.A, R5.2
unnamed: I2C_PU.3, R14.2
unnamed: D3.A, R12.2
unnamed: I2C_PU.1, R15.2
unnamed: D5.A, R6.2
unnamed: ALED1.2, D5.C
unnamed: D1.C, PLED1.2
unnamed: C13.1, U1.6
unnamed: C13.2, L2.P$1, U1.5
unnamed: D6.A, R10.2
unnamed: D6.C, RLED1.2
unnamed: ALED.2, D3.C
unnamed: J12.B5, R16.2
unnamed: D2.C, PLED.2
unnamed: J12.A5, R13.2
unnamed: I2C_PU2.3, R17.2
unnamed: I2C_PU2.1, R18.2
unnamed: D7.A, R19.2
unnamed: D8.A, R20.2
unnamed: ALED2.2, D8.C
unnamed: D7.C, PLED2.2
unnamed: C27.1, U6.6
unnamed: C27.2, L3.P$1, U6.5
unnamed: D9.A, R22.2
unnamed: D9.C, RLED2.2
unnamed: J19.B5, R24.2
unnamed: J19.A5, R23.2
unnamed: I2C_PU3.3, R25.2
unnamed: I2C_PU3.1, R26.2
unnamed: D10.A, R27.2
unnamed: D11.A, R28.2
unnamed: ALED3.2, D11.C
unnamed: D10.C, PLED3.2
unnamed: C40.1, U10.6
unnamed: C40.2, L4.P$1, U10.5
unnamed: D12.A, R30.2
unnamed: D12.C, RLED3.2
unnamed: J26.B5, R32.2
unnamed: J26.A5, R31.2
unnamed: I2C_PU4.3, R33.2
unnamed: I2C_PU4.1, R34.2
unnamed: D13.A, R35.2
unnamed: D14.A, R36.2
unnamed: ALED4.2, D14.C
unnamed: D13.C, PLED4.2
unnamed: C53.1, U13.6
unnamed: C53.2, L5.P$1, U13.5
unnamed: D15.A, R38.2
unnamed: D15.C, RLED4.2
unnamed: J33.B5, R40.2
unnamed: J33.A5, R39.2
unnamed: I2C_PU5.3, R41.2
unnamed: I2C_PU5.1, R42.2
unnamed: D16.A, R43.2
unnamed: D17.A, R44.2
unnamed: ALED5.2, D17.C
unnamed: D16.C, PLED5.2
unnamed: C66.1, U16.6
unnamed: C66.2, L6.P$1, U16.5
unnamed: D18.A, R46.2
unnamed: D18.C, RLED5.2
unnamed: J40.B5, R48.2
unnamed: J40.A5, R47.2
SHLD: J3.SHLD1, J3.SHLD2, J3.SHLD3, J3.SHLD4, J3.SHLD5, J3.SHLD6, J3.SHLD7, J3.SHLD8, SHLD.2
SHLD1: J12.SHLD1, J12.SHLD2, J12.SHLD3, J12.SHLD4, J12.SHLD5, J12.SHLD6, J12.SHLD7, J12.SHLD8, SHLD1.2
SHLD2: J19.SHLD1, J19.SHLD2, J19.SHLD3, J19.SHLD4, J19.SHLD5, J19.SHLD6, J19.SHLD7, J19.SHLD8, SHLD2.2
SHLD3: J26.SHLD1, J26.SHLD2, J26.SHLD3, J26.SHLD4, J26.SHLD5, J26.SHLD6, J26.SHLD7, J26.SHLD8, SHLD3.2
SHLD4: J33.SHLD1, J33.SHLD2, J33.SHLD3, J33.SHLD4, J33.SHLD5, J33.SHLD6, J33.SHLD7, J33.SHLD8, SHLD4.2
SHLD5: J40.SHLD1, J40.SHLD2, J40.SHLD3, J40.SHLD4, J40.SHLD5, J40.SHLD6, J40.SHLD7, J40.SHLD8, SHLD5.2
VIN: C1.1, J1.1, J3.VBUS1, J3.VBUS2, R3.2, U2.3, U5.5
VIN1: C17.1, J12.VBUS1, J12.VBUS2, J13.1, R9.2, U1.3, U3.5
VIN2: C30.1, J19.VBUS1, J19.VBUS2, J20.1, R21.2, U6.3, U8.5
VIN3: C43.1, J26.VBUS1, J26.VBUS2, J27.1, R29.2, U10.3, U11.5
VIN4: C56.1, J33.VBUS1, J33.VBUS2, J34.1, R37.2, U13.3, U14.5
VIN5: C69.1, J40.VBUS1, J40.VBUS2, J41.1, R45.2, U16.3, U17.5

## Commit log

2023-02-01 Moves parts around
2023-02-02 Routes board
2023-02-03 Commits (finally) to shrinking the LED resistors so that I can fit in labels
    * Increases schematic frame size to Ledger
    * Adds measures
    * Adds additional silk
2023-03-01 Replaces UART IC
    * Cuts back ground pour to make room for smaller modules RF singnals
    * Fixes polygons
    * Adds yellow LED
    * Adds additional decoupling caps for RF board
    * Increases the size of the board by 0.1" to make space for decoupling caps
    * Updates the inductor for switching regulator
2023-03-02 Routes some airwires
2023-03-02 Finishes routing airwires, fixes silk
2023-03-02 Adds many GND vias
    * Adds ordering instructions
    * Changes VUSB net to VIN for consistency with other Xbee products
2023-03-03 Replaces RED LED with the correct one
2023-03-03 Approves various DRC issues
2023-03-03 Renames board files
2023-03-03 Adds "Explorer" to silk
2023-03-08 Adds 4.7uF decoupling cap to FTDI
2023-03-08 Fixes anchors on some title labels in the schematic, adds more vias
    * Increases the size of the Qwiic logo
2023-03-08 Adds Production Files
2023-03-09 Updates panel to be 3x2
2023-03-09 Renames production zip file to include version number
2023-08-02 Initial pass of documentation
2023-09-13 Periodic checkin
2023-09-18 Updating tables and removing unnecessary files
2023-09-18 Update link to product image
2023-09-18 Fix autofill error
2023-09-18 Updating hardware overview images
2023-09-18 Adding FT231XS to Overview
2023-09-18 Fixing links
2023-11-30 Updating action shots and file resources
2023-11-30 Adding description and formatting rec Reading
2023-11-30 Updating action shot and single page
2023-12-12 Adding setuptools to build
2023-12-22 Update to add Qwiic connex to overview
2024-01-03 Updates to intro and overview
2024-01-05 Updates to trademarks per Digi
2024-01-05 Updates for consistency
2024-01-08 Update hardware_overview.md per Eli notes
2024-01-08 Deployed 97aaf06 with MkDocs version: 1.5.3
2024-05-17 Deployed dcc43d2 with MkDocs version: 1.6.0
2026-06-03 Deployed 25cb152 with MkDocs version: 1.6.1

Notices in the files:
parts and their libraries:
SparkFun-Capacitors: Licensing: Creative Commons ShareAlike 4.0 International - https://creativecommons.org/licenses/by-sa/4.0
SparkFun-Aesthetics: Released under the Creative Commons Attribution Share-Alike 4.0 License
SparkFun-Aesthetics: https://creativecommons.org/licenses/by-sa/4.0
